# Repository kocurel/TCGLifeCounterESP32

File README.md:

# An electronic ESP32-C3-powered life counter for Trading Card Games. 
## Made with the players of Magic the Gathering and Yu-Gi-Oh in mind.

The main goal for this project was to implement the basic LifeTap features.
I expanded on some of the features by tracking more variables 
(letting the player rename the value names as they see fit).

Anticipating players making mistakes, the device tracks change history 
letting the player undo to a selected point in time.

As an added extra, I included a dice page that lets the user simulate dice throws using esp_random().
The included dice options are (coin, d3, d4, d6, d8, d10, d12, d20, d100). It's possible to throw 1-4 dice at once and reroll any of the results.

A 3D render generated in Kicad

# The main interface

# Hardware
The main components of the device are:
1. [SEEED XIAO ESP32-C3](https://botland.store/esp32-wifi-and-bt-modules/21859-seeed-xiao-esp32-c3-wifibluetooth-seeedstudio-113991054.html)
2. [msalamon SSD1309 2.42" OLED display](https://sklep.msalamon.pl/produkt/wyswietlacz-oled-242-128x64px-niebieski/)
3. [A 3x3 12x12mm tactile switch matrix](https://www.tme.eu/pl/en/details/ts24n/microswitches-tact/knitter-switch/ts-24-n/)
4. A passive buzzer
5. 10x 1N4148 diodes
6. A 1050mAh LiPo battery

## The schematics

# Software
When I made the project I used three main components:
1. ESP-IDF
2. [u8g2](https://github.com/olikraus/u8g2)
3. [u8g2-hal-esp-idf](https://github.com/mkfrey/u8g2-hal-esp-idf)

## GUIFramework

When designing this device I expected I would need a way to easily design a UI.
I decided to go with a grid-like system using Labels nested in VBoxes and HBoxes.
For an easier time programming I tried to emulate inheritance and OOP in C using vtables.

Later on, I added a GUIList component that uses the delegate design pattern to access the underlying data.

Using nested containers I was able to get perfectly even grids in my UI without too many manual adjustments.
The navigation pointers inside the GUIComponent made designing the UI navigation really easy.
For extra simplicity I added GUI_LINK_VERTICAL and GUI_LINK_HORIZONTAL macros that automatically assign the pointers.

# About the firmware
## The features
For a better user experience I included a few extra features:
1. Battery level tracking (using ADC and a simple linear interpolation).
2. Automatic, adjustable display timeout to save battery life.
3. Automatic, adjustable power-off (deep sleep) under extended inactivity.
4. Long press of any of the switches reads as multiple presses, going into turbo mode when held for over 1.2s.

## The non-volatile storage
I used NVS to store data between sessions:
1. Device settings
2. Player names
3. Value names

## FreeRTOS
I went with a modular design based on FreeRTOS tasks for easy concurrency handling.
The main tasks include:
1. The main loop that handles rendering and input handling
2. The keypad task that scans the key matrix every 5 ms
3. The battery level read task that reads the battery level every 1 s
4. The audio manager task that uses a non-blocking queue for audio playback

In the development stage I used a command line task to emulate keypad input
that I really don't use anymore but I left it in the code
just in case I have a use for it in the future.

## The buzzer
The buzzer was added so the device has audible feedback on stuff like errors and device waking up.
I control it using the LEDC library of ESP-IDF to play simple tones.

## The key matrix
To save GPIO pins I went with a 3x3 switch matrix. I run a FreeRTOS task that scans the matrix every 5 ms.
For debouncing I use 8 bit unsigned integers as software shift registers. When the last three bits of the register are 1's
the matrix reads a press. Similarly, when the last 3 bits of the register are 0's the matrix reads a release.

## The display
To ensure a smooth user experience, I interface with the SSD1309 OLED display via I2C at 800 kHz. 
This high clock speed allows for fluid animations and a high UI refresh rate.

To minimize standby current draw during inactivity, I implemented a PMOS high-side switch circuit. 
This allows the firmware to completely cut off the VCC rail of the display, effectively extending the battery life.

**In this prototype I have not yet introduced a way to permanently save game state between sessions**

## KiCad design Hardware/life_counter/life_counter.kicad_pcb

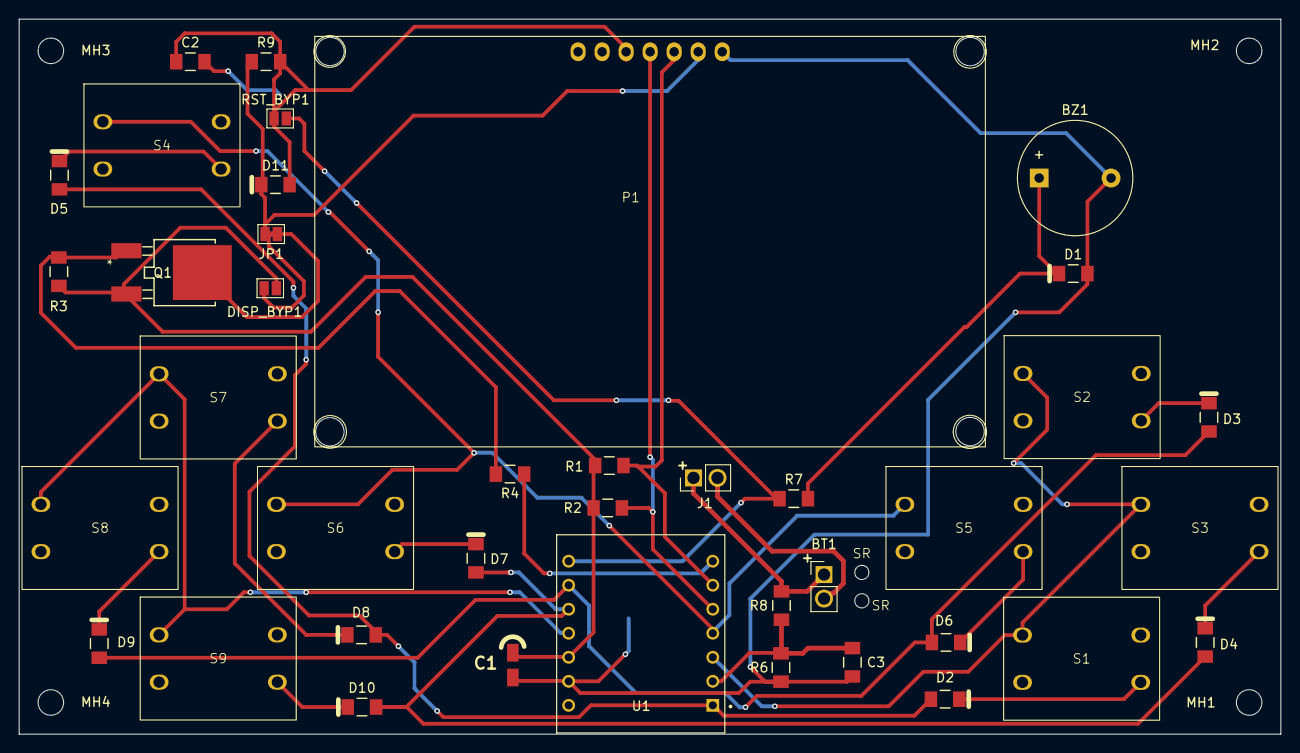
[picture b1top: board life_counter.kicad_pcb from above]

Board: 2 copper layers, 133.4 x 75.6 mm, 46 parts (0 on the bottom side), 29 nets.

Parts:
BT1: Battery_Cell; PinHeader_1x02_P2.54mm_Vertical
BZ1: Buzzer; Buzzer_12x9.5RM7.6
C1: 100uF; T520A
C2, C3: 100nF; RC1206N_YAG-M
D1, D2, D3, D4, D5, D6, D7, D8, D9, D10, D11: 1N4148; CD4148W(1206C)
DISP_BYP1: Jumper_2_Open; SolderJumper-2_P1.3mm_Open_Pad1.0x1.5mm
J1: XIAO_BAT_LINK; PinHeader_1x02_P2.54mm_Vertical
JP1: Jumper_2_Bridged; SolderJumper-2_P1.3mm_Bridged_Pad1.0x1.5mm
MH1, MH2, MH3, MH4: MountingHole_2.7mm_M2.5
P1: OLED-DISPLAY; 2.42in128x64OLED
Q1: Q-PMOS; DPAK-4_6P22X6P73_ONS-M
R1, R2, R4: 4k7; RC1206N_YAG-M
R3, R6: 330k; RC1206N_YAG-M
R7: 200; RC1206N_YAG-M
R8: 680k; RC1206N_YAG-M
R9: 10k; RC1206N_YAG-M
RST_BYP1: Jumper_2_Open; SolderJumper-2_P1.3mm_Open_Pad1.0x1.5mm
S1, S2, S3, S4, S5, S6, S7, S8, S9: TS-24-N; TS_24_N_SWITCH
SR: Cable_strain_relief_1.5mm
SR#2: Cable_strain_relief_1.5mm
U1: XIAO ESP32C3; MODULE_113991054

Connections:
+3V3: C1.1 (+), DISP_BYP1.1 (A), Q1.3 (S), R1.1, R2.1, R3.1, U1.12 (VCC_3V3)
/BAT+: BT1.1 (+), J1.1, R8.1
/BAT-: BT1.2 (-), J1.2
/BAT_RD: C3.1, R6.1, R8.2, U1.2 (D1)
/BUZZER: R7.1, RST_BYP1.2 (B), U1.8 (D7)
/Button_matrix/COL0: D2.2, D5.2, D8.2, U1.1 (D0)
/Button_matrix/COL1: D3.2, D6.2, D9.2, U1.9 (D8)
/Button_matrix/COL2: D4.2, D7.2, D10.2, U1.10 (D9)
/Button_matrix/ROW0: S1.1, S2.1, S3.1, U1.3 (D2)
/Button_matrix/ROW1: S4.1, S5.1, S6.1, U1.4 (D3)
/Button_matrix/ROW2: S7.1, S8.1, S9.1, U1.11 (D10)
/DISP_VCC: JP1.1 (A), Q1.4 (D)
/SCL: P1.3 (SCK), R1.2, U1.6 (D5)
/SDA: P1.4 (SDA), R2.2, U1.5 (D4)
/~DISP_EN: R4.1, U1.7 (D6)
GND: BZ1.2 (-), C1.2 (-), C2.2, C3.2, D1.2, P1.1 (GND), R6.2, U1.13 (GND)
unnamed: BZ1.1 (+), D1.1, R7.2
unnamed: D2.1, S1.4
unnamed: D3.1, S2.4
unnamed: D4.1, S3.4
unnamed: D5.1, S4.4
unnamed: D6.1, S5.4
unnamed: D7.1, S6.4
unnamed: D8.1, S7.4
unnamed: D9.1, S8.4
unnamed: D10.1, S9.4
unnamed: D11.1, DISP_BYP1.2 (B), JP1.2 (B), P1.2 (VCC), R9.1
unnamed: C2.1, D11.2, P1.5 (RES), R9.2, RST_BYP1.1 (A)
unnamed: Q1.1 (G), R3.2, R4.2

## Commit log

2025-12-11 added a few tests
2025-12-11 added more tests
2025-12-12 refactored for static allocation
2025-12-12 added navigation function pointers to components for easier menu navigation setup
2025-12-13 removed memset and added GUI_ADD_CHILDREN() for easier layout management
2025-12-13 added GUIList
2025-12-13 modified file structure, added PlayerPage
2025-12-13 added commander damage page
2025-12-14 fixed centering in CommanderPage
2025-12-14 added ValueEditorPage
2025-12-14 ValuePageEditor now displays properly
2025-12-14 VALuePageEditor almost ready
2025-12-14 added the callback to PlayerPage from ValueEditorPage
2025-12-14 added the MenuPage
2025-12-16 history page
2026-01-14 moved to linux
2026-01-14 configured the project esp to work on linux
2026-01-28 configured the display, buttons and battery read
2026-01-29 kill ledc on sleep
2026-01-30 MVP complete
2026-01-30 added player name change
2026-01-31 idfk, zmiana UI main page
2026-01-31 value names page, fixed dice page
2026-01-31 code cleanup (comments)
2026-01-31 shortened max string length
2026-02-06 final
2026-04-17 cleanup
2026-04-17 added the hardware kicad project
2026-04-19 docs: improve technical documentation in core modules
2026-04-23 Add README for ESP32-C3 life counter project
2026-04-23 Fix typos and improve README formatting
2026-04-23 updated the kicad schematics, added auto shut off when battery is at 3.3V, added an image folder forthe github page
2026-04-23 Add image to README for device representation
2026-04-23 Add description for 3D render in README
    Added a description for the 3D render in Kicad.
2026-04-23 Add software components section to README
    Added section about software components used in the project.
2026-04-23 Update README with hardware and software details
    Added hardware and software sections to the README.
2026-04-23 added a GUI diagram png
2026-04-23 Fix typo in image source of guiclassdiagram
2026-04-23 Update image width in GUI section of README
2026-04-23 Rename 'GUI Library' to 'GUIFramework' and expand details
    Updated section title and added description for GUI framework.
2026-04-23 added images
2026-04-23 Update README with UI layout improvements
    Added a note about using nested containers for even grids.
2026-04-23 Update README with GUIList component details
    Added information about the GUIList component and UI adjustments.
2026-04-23 Enhance README with UI navigation details
    Added a section about navigation pointers and macros for UI design.
2026-04-23 Clarify UI navigation design explanation
    Reworded a sentence for clarity.
2026-04-23 Enhance README with project details and features
    Expanded project description to include additional features and functionality.
2026-04-23 Fix wording in README for clarity
2026-04-23 Revise README for clarity and additional details
    Updated formatting and added sections for firmware features, non-volatile storage, and FreeRTOS design.
2026-04-23 Update README with buzzer and key matrix details
    Added sections on buzzer functionality and key matrix design.
2026-04-23 Fix typos in README.md
    Corrected typos in the README, including 'nexted' to 'nested' and 'shut 0off' to 'shut-off'.
2026-04-23 added schematic as pngs
2026-04-23 Add schematics section to README
    Added schematics section with images to README.
2026-04-23 added main page images
2026-04-23 Update README with main interface images
    Added images and section for the main interface.
2026-04-23 Refactor image section in README.md
    Removed redundant line breaks and adjusted image formatting.
2026-04-23 Fix typos in README.md for clarity
2026-04-23 Fix typo in README regarding standby current draw
2026-04-23 Include dice simulation feature in README
    Added a dice simulation feature allowing users to throw multiple dice types and reroll results.
2026-04-23 Fix grammar in README dice options section
    Corrected grammar in dice options description.
2026-04-24 Update SEEED XIAO ESP32-C3 link in README
2026-05-15 Fix spelling errors in README
    Corrected spelling errors in README.md.
